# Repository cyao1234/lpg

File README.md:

# UC ULP GMSS & LTE-M SiP DK

This is a high efficiency ULP SIP GMSS, NBIoT & LTE-M nRF91 STO LTS for IOT with minimal BOM, ultra-low Iq and dedicated STO PHY (IP). It operates with an advanced LP PSM paired with an low iDRX interval RRC idle to optimize RX dBm gain using cDRX variations and variable iDRX PDCCH.

With integrated FETs, LNA and FIDOs, it becomes the perfect LPWA GMSS & NBIoT DK. The only external UE needed is an active IPEX U.FE RoHS MHFI antenna (50 ohms) connected to the on-board SWF. It enables remote HWFC TXD via SWO thanks to it's subscriber identity module.

## Features

- 3x3cm UC footprint
- < 500uA current consumtion
- Embedded UART FTDI TXD via USB 2.0
- External MMC (32MiB)
- GPIO breakouts
- IPEX U.FE MHFI ANT connectors
- JST PH B2B LiPo connection
- Self contained

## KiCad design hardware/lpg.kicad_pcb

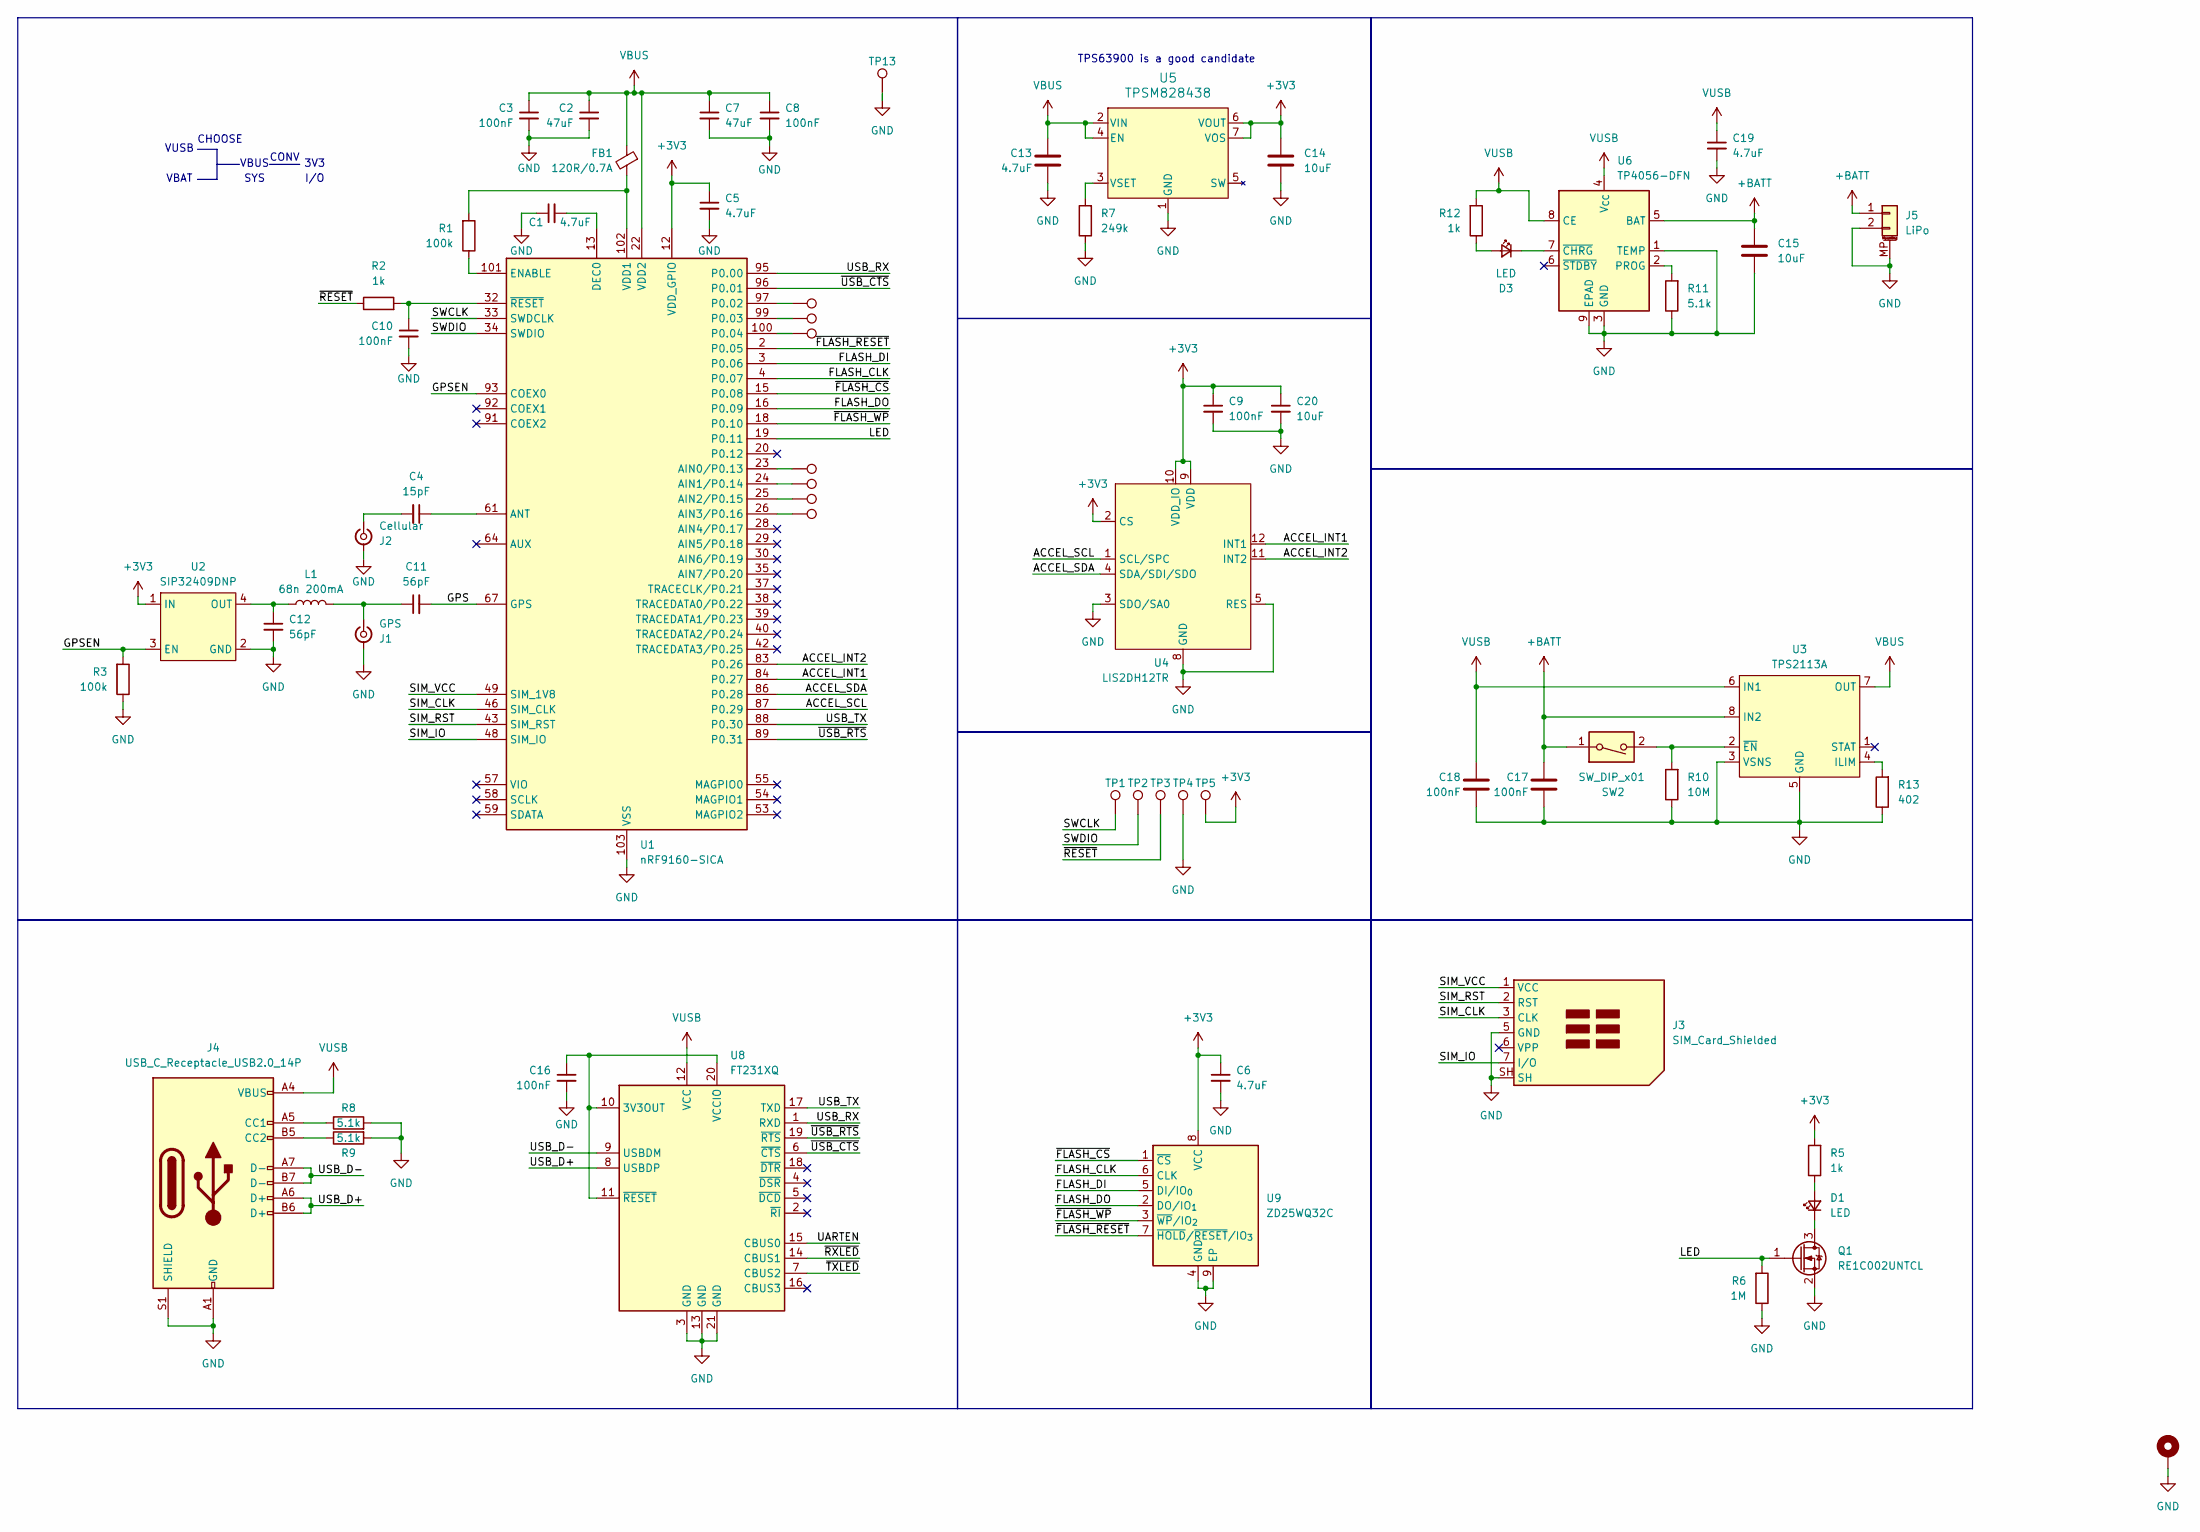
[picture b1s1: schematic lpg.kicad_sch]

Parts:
C1, C5, C6, C13, C19: 4.7uF; C_0402_1005Metric; LCSC Part # C23733
C2, C7: 47uF; C_0603_1608Metric; LCSC Part # C140782
C3, C8, C9, C10, C16, C17, C18: 100nF; C_0402_1005Metric; LCSC Part # C60474
C4: 15pF; C_0402_1005Metric; LCSC Part # C1548
C11, C12: 56pF; C_0402_1005Metric; LCSC Part # C107007
C14, C15, C20: 10uF; C_0402_1005Metric; LCSC Part # C315248
D1, D3: LED; LED_0402_1005Metric; LCSC Part # C779449
FB1: 120R/0.7A; L_0402_1005Metric; LCSC Part # C88970
H1: MountingHole_Pad_MP; MountingHole_2.2mm_M2
J1: GPS; U.FL_Hirose_U.FL-R-SMT-1_Vertical; LCSC Part # C88374
J2: Cellular; U.FL_Hirose_U.FL-R-SMT-1_Vertical; LCSC Part # C88374
J3: SIM_Card_Shielded; SMN-304; LCSC Part # C266889
J4: USB_C_Receptacle_USB2.0_14P; USB_C_Receptacle_HRO_TYPE-C-31-M-12; LCSC Part # C165948
J5: LiPo; JST_PH_B2B-PH-K_1x02_P2.00mm_Vertical; LCSC Part # C2319
L1: 68n 200mA; L_0402_1005Metric; LCSC Part # C391307
Q1: RE1C002UNTCL; SC-89; LCSC Part # C509959
R1, R3: 100k; R_0402_1005Metric; LCSC Part # C25741
R2, R5, R12: 1k; R_0402_1005Metric; LCSC Part # C11702
R6: 1M; R_0402_1005Metric; LCSC Part # C26083
R7: 249k; R_0402_1005Metric; LCSC Part # C11425
R8, R9, R11: 5.1k; R_0402_1005Metric; LCSC Part # C25905
R10: 10M; R_0402_1005Metric; LCSC Part # C26082
R13: 402; R_0402_1005Metric; LCSC Part # C2933096
SW2: SW_DIP_x01; EU-01KS; LCSC Part # C47817623
TP1, TP2, TP3, TP4, TP5, TP6, TP7, TP8, TP9, TP10, TP11, TP12, TP13: TestPoint; TestPoint_Pad_D1.5mm
U1: nRF9160-SICA; Nordic_nRF9160-SIxx_LGA-102-59EP_16.0x10.5mm_P0.5mm; LCSC Part # C1518973
U2: SIP32409DNP; TDFN-4-1.2x1.6; LCSC Part # C145277
U3: TPS2113A; VSON-8-1EP_3x3mm_P0.65mm_EP1.65x2.4mm_ThermalVias; LCSC Part # C354512
U4: LIS2DH12TR; LGA-12_2x2mm_P0.5mm; LCSC Part # C110926
U5: TPSM828438; VCF0007A-MFG; LCSC Part # C44545617
U6: TP4056-DFN; DFN-8-1EP_2x2mm_P0.5mm_EP0.9x1.6mm; LCSC Part # C49208530
U8: FT231XQ; QFN-20-1EP_4x4mm_P0.5mm_EP2.5x2.5mm; LCSC Part # C132159
U9: ZD25WQ32C; Winbond_USON-8-1EP_3x2mm_P0.5mm_EP0.2x1.6mm; LCSC Part # C5258281

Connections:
+3V3: C5.1, C6.1, C9.1, C14.1, C20.1, R5.2, TP5.1, U1.12 (VDD_GPIO), U2.1 (IN), U4.2 (CS), U4.9 (VDD), U4.10 (VDD_IO), U5.6 (VOUT), U5.7 (VOS), U9.8 (VCC)
+BATT: C15.1, C17.1, J5.1, SW2.1, U3.8 (IN2), U6.5 (BAT)
/ACCEL_INT1: U1.84 (P0.27), U4.12 (INT1)
/ACCEL_INT2: U1.83 (P0.26), U4.11 (INT2)
/ACCEL_SCL: U1.87 (P0.29), U4.1 (SCL/SPC)
/ACCEL_SDA: U1.86 (P0.28), U4.4 (SDA/SDI/SDO)
/FLASH_CLK: U1.4 (P0.07), U9.6 (CLK)
/FLASH_DI: U1.3 (P0.06), U9.5 (DI/IO_{0})
/FLASH_DO: U1.16 (P0.09), U9.2 (DO/IO_{1})
/GPS: C11.2, U1.67 (GPS)
/GPSEN: R3.2, U1.93 (COEX0), U2.3 (EN)
/LED: Q1.1 (G), R6.2, U1.19 (P0.11)
/SIM_CLK: J3.3 (CLK), U1.46 (SIM_CLK)
/SIM_IO: J3.7 (I/O), U1.48 (SIM_IO)
/SIM_RST: J3.2 (RST), U1.43 (SIM_RST)
/SIM_VCC: J3.1 (VCC), U1.49 (SIM_1V8)
/SWCLK: TP1.1, U1.33 (SWDCLK)
/SWDIO: TP2.1, U1.34 (SWDIO)
/UARTEN: U8.15 (CBUS0)
/USB_D+: J4.A6 (D+), J4.B6 (D+), U8.8 (USBDP)
/USB_D-: J4.A7 (D-), J4.B7 (D-), U8.9 (USBDM)
/USB_RX: U1.95 (P0.00), U8.1 (RXD)
/USB_TX: U1.88 (P0.30), U8.17 (TXD)
/~FLASH_CS: U1.15 (P0.08), U9.1 (~CS)
/~FLASH_RESET: U1.2 (P0.05), U9.7 (~HOLD/~RESET/IO_{3})
/~FLASH_WP: U1.18 (P0.10), U9.3 (~WP/IO_{2})
/~RESET: R2.1, TP3.1
/~RXLED: U8.14 (CBUS1)
/~TXLED: U8.7 (CBUS2)
/~USB_CTS: U1.96 (P0.01), U8.6 (~CTS)
/~USB_RTS: U1.89 (P0.31), U8.19 (~RTS)
GND: C1.1, C2.2, C3.2, C5.2, C6.2, C7.2, C8.2, C9.2, C10.2, C12.2, C13.2, C14.2, C15.2, C16.2, C17.2, C18.2, C19.2, C20.2, H1.MP, J1.2 (Ext), J2.2 (Ext), J3.5 (GND), J3.SH, J4.A1 (GND), J4.A12 (GND), J4.B1 (GND), J4.B12 (GND), J4.S1 (SHIELD), J5.2, J5.MP (MountPin), Q1.2 (S), R3.1, R6.1, R7.1, R8.2, R9.2, R10.1, R11.1, R13.1, TP4.1, TP13.1, U1.1 (GND_Shield), U1.5 (GND_Shield), U1.6 (GND_Shield), U1.7 (GND_Shield), U1.8 (GND_Shield), U1.9 (GND_Shield), U1.11 (GND_Shield), U1.14 (GND_Shield), U1.17 (GND_Shield), U1.21 (GND_Shield), U1.27 (GND_Shield), U1.31 (GND_Shield), U1.36 (GND_Shield), U1.41 (GND_Shield), U1.44 (GND_Shield), U1.47 (GND_Shield), U1.50 (GND_Shield), U1.52 (GND_Shield), U1.56 (GND_Shield), U1.60 (GND_Shield), U1.62 (GND_Shield), U1.63 (GND_Shield), U1.65 (GND_Shield), U1.66 (GND_Shield), U1.68 (GND_Shield), U1.69 (GND_Shield), U1.72 (GND_Shield), U1.74 (GND_Shield), U1.75 (GND_Shield), U1.76 (GND_Shield), U1.77 (GND_Shield), U1.78 (GND_Shield), U1.79 (GND_Shield), U1.80 (GND_Shield), U1.81 (GND_Shield), U1.82 (GND_Shield), U1.85 (GND_Shield), U1.90 (GND_Shield), U1.94 (GND_Shield), U1.98 (GND_Shield), U1.103 (VSS), U2.2 (GND), U2.5 (GND), U3.3 (VSNS), U3.5 (GND), U3.9 (GND), U4.3 (SDO/SA0), U4.5 (RES), U4.6 (GND), U4.7 (GND), U4.8 (GND), U5.1 (GND), U6.1 (TEMP), U6.3 (GND), U6.9 (EPAD), U8.3 (GND), U8.13 (GND), U8.21 (GND), U9.4 (GND), U9.9 (EP)
unnamed: D1.2 (A), R5.1
unnamed: D1.1 (K), Q1.3 (D)
unnamed: D3.2 (A), R12.1
unnamed: D3.1 (K), U6.7 (~CHRG)
unnamed: C11.1, J1.1 (In), L1.2
unnamed: C4.2, J2.1 (In)
unnamed: J4.A5 (CC1), R8.1
unnamed: J4.B5 (CC2), R9.1
unnamed: TP9.1, U1.23 (AIN0/P0.13)
unnamed: TP10.1, U1.24 (AIN1/P0.14)
unnamed: TP11.1, U1.25 (AIN2/P0.15)
unnamed: TP12.1, U1.26 (AIN3/P0.16)
unnamed: C4.1, U1.61 (ANT)
unnamed: C1.2, U1.13 (DEC0)
unnamed: R1.1, U1.101 (ENABLE)
unnamed: TP8.1, U1.97 (P0.02)
unnamed: TP7.1, U1.99 (P0.03)
unnamed: TP6.1, U1.100 (P0.04)
unnamed: FB1.2, R1.2, U1.102 (VDD1)
unnamed: C10.1, R2.2, U1.32 (~RESET)
unnamed: C12.1, L1.1, U2.4 (OUT)
unnamed: R13.2, U3.4 (ILIM)
unnamed: R10.2, SW2.2, U3.2 (~EN)
unnamed: R7.2, U5.3 (VSET)
unnamed: R11.2, U6.2 (PROG)
unnamed: C16.1, U8.10 (3V3OUT), U8.11 (~RESET), U8.20 (VCCIO)
VBUS: C2.1, C3.1, C7.1, C8.1, C13.1, FB1.1, U1.22 (VDD2), U3.7 (OUT), U5.2 (VIN), U5.4 (EN)
VUSB: C18.1, C19.1, J4.A4 (VBUS), J4.A9 (VBUS), J4.B4 (VBUS), J4.B9 (VBUS), R12.2, U3.6 (IN1), U6.4 (V_{CC}), U6.8 (CE), U8.12 (VCC)

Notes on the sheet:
VUSB
VBAT
I/O
3V3
VBUS
CHOOSE
TPS63900 is a good candidate
CONV
SYS

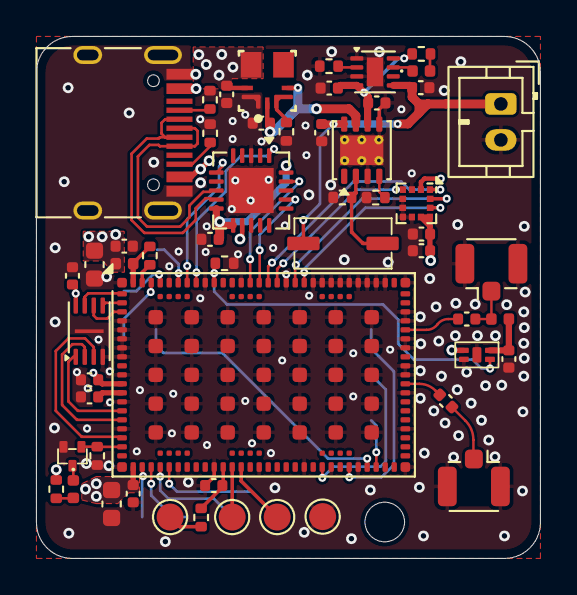
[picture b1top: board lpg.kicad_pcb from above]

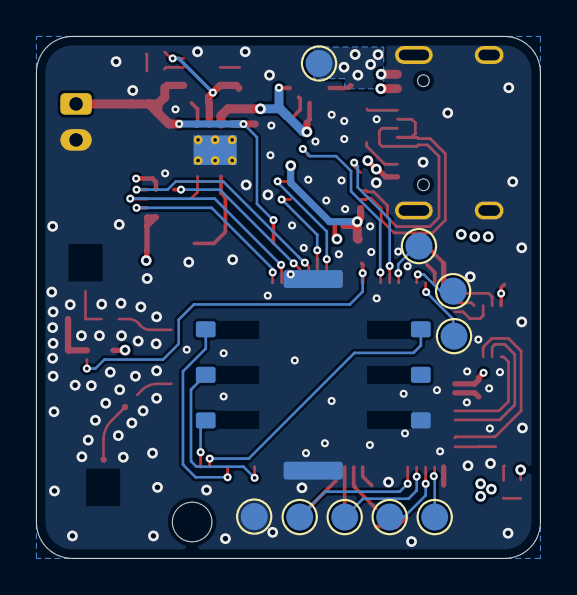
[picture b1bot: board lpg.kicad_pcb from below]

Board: 4 copper layers, 28.0 x 29.0 mm, 65 parts (10 on the bottom side), 57 nets.

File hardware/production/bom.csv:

Designator,Footprint,Quantity,Value,LCSC Part #
"C1, C13, C19, C5, C6",0402,5,4.7uF,C23733
"C10, C16, C17, C18, C3, C8, C9",0402,7,100nF,C60474
"C11, C12",0402,2,56pF,C107007
"C14, C15, C20",0402,3,10uF,C315248
"C2, C7",0603,2,47uF,C140782
C4,0402,1,15pF,C1548
"D1, D3",0402,2,LED,C779449
FB1,0402,1,120R/0.7A,C88970
"J1, J2",U.FL_Hirose_U.FL-R-SMT-1_Vertical,2,GPS,C392444
J3,SMN-304,1,SIM_Card_Shielded,C266889
J4,USB_C_Receptacle_HRO_TYPE-C-31-M-12,1,USB_C_Receptacle_USB2.0_14P,C165948
J5,JST_PH_B2B-PH-K_1x02_P2.00mm_Vertical,1,LiPo,C2319
L1,0402,1,68n 200mA,C391307
Q1,SC-89,1,RE1C002UNTCL,C509959
"R1, R3",0402,2,100k,C25741
R10,0402,1,10M,C26082
"R11, R8, R9",0402,3,5.1k,C25905
"R12, R2, R5",0402,3,1k,C11702
R13,0402,1,402,C2933096
R6,0402,1,1M,C26083
R7,0402,1,249k,C11425
SW2,EU-01KS,1,SW_DIP_x01,C47817623
U1,Nordic_nRF9160-SIxx_LGA-102-59EP_16.0x10.5mm_P0.5mm,1,nRF9160-SICA,C1518973
U2,TDFN-4-1.2x1.6,1,SIP32409DNP,C145277
U3,VSON-8-1EP_3x3mm_P0.65mm_EP1.65x2.4mm_ThermalVias,1,TPS2113A,C354512
U4,LGA-12_2x2mm_P0.5mm,1,LIS2DH12TR,C110926
U5,VCF0007A-MFG,1,TPSM828438,C44545617
U6,DFN-8-1EP_2x2mm_P0.5mm_EP0.9x1.6mm,1,TP4056-DFN,C49208530
U8,QFN-20-1EP_4x4mm_P0.5mm_EP2.5x2.5mm,1,FT231XQ,C132159
U9,Winbond_USON-8-1EP_3x2mm_P0.5mm_EP0.2x1.6mm,1,ZD25WQ32C,C5258281

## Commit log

2026-01-16 Init
